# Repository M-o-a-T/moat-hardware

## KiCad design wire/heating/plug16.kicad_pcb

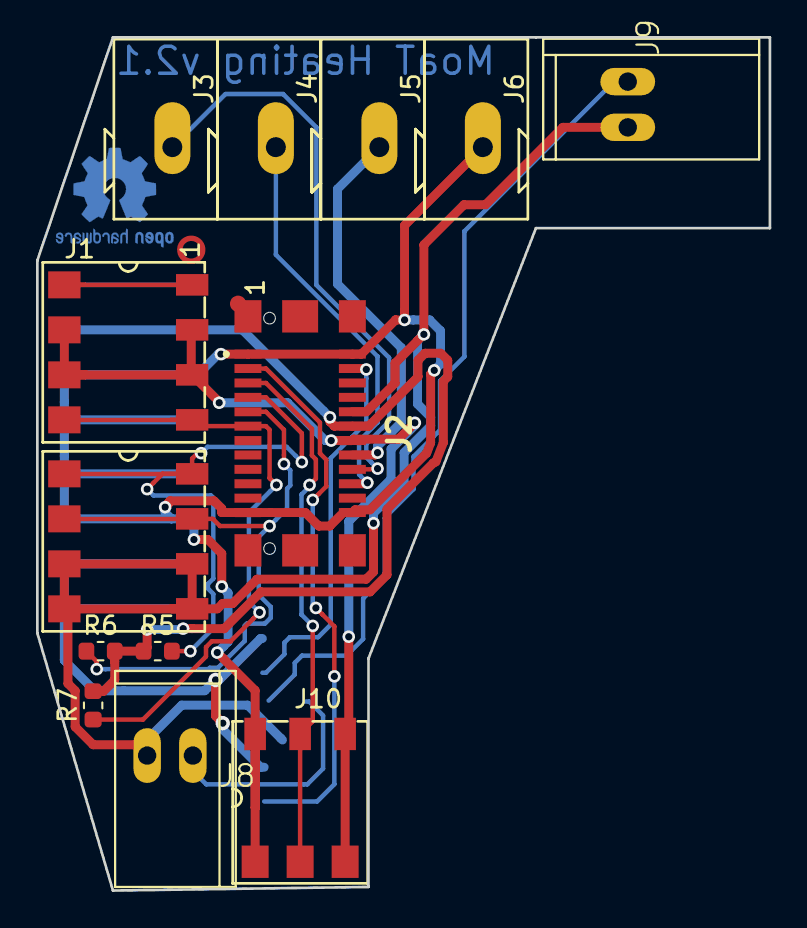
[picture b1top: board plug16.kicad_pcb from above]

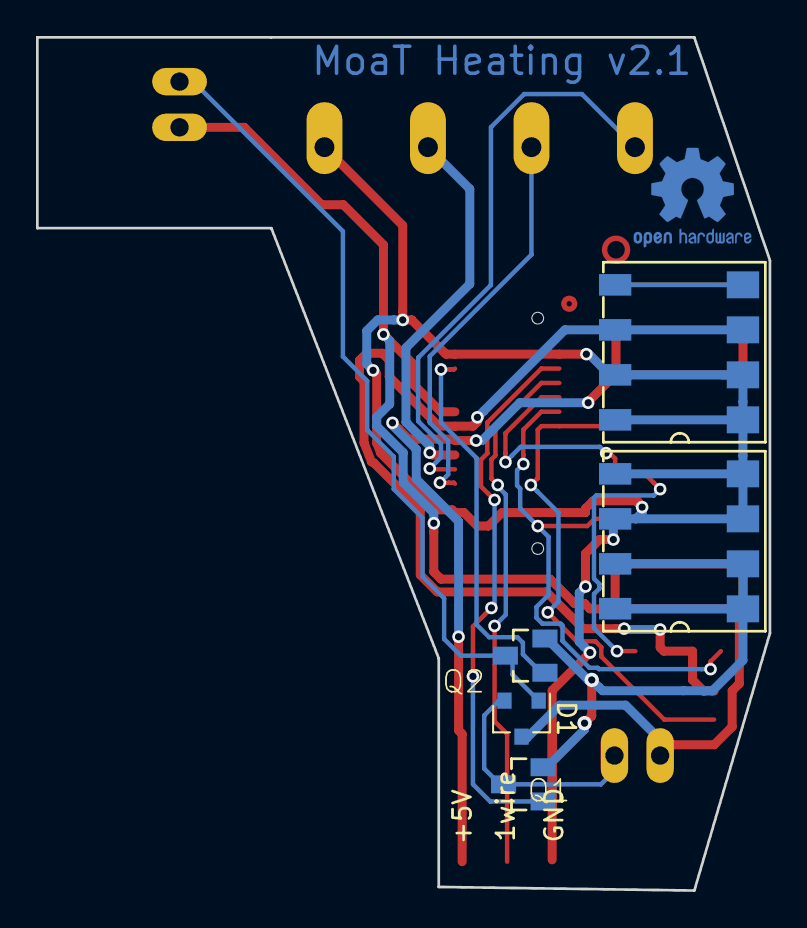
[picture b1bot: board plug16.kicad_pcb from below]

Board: 2 copper layers, 40.7 x 47.4 mm, 15 parts (3 on the bottom side), 16 nets.

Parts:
D1: BAT54C; SOT-23
J1: Moat_Bus_16; Moat_16_2side
J2: Moat_Bus_wire; TE_1775014_socket
J3: SCLK; Wago_Terminal_243
J4: SDA; Wago_Terminal_243
J5: 3V3; Wago_Terminal_243
J6: GND; Wago_Terminal_243
J8: S1; 1X02_GN
J9: S2; 1X02_GN
J10: 1wireConn; AVX_9276_3Pin
Q1, Q2: 2N7002; SOT23
R5, R6, R7: 470; R_0603_1608Metric

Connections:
/S1: J2.3, Q1.1
/S2: J2.4, Q2.1
GNDPWR: J1.14, J1.16, Q1.2, Q2.2
unnamed: D1.1, J9.1, Q2.3
unnamed: D1.2, J8.1, Q1.3
unnamed: D1.3, J1.13, J1.15, J2.10, J8.2, J9.2
unnamed: J1.3, J1.5, J2.14, J10.3
unnamed: J1.4, J2.12, R5.1, R6.2, R7.2
unnamed: J1.7, J2.11, R7.1
unnamed: J1.9, J2.7, R5.2
unnamed: J1.6, J1.8, J1.10, J1.12, J2.1, J2.2, J2.23, J2.24, J6.1, J10.1
unnamed: J1.11, J2.9, R6.1
unnamed: J2.16, J5.1
unnamed: J2.18, J3.1
unnamed: J2.20, J4.1
unnamed: J2.5, J10.2

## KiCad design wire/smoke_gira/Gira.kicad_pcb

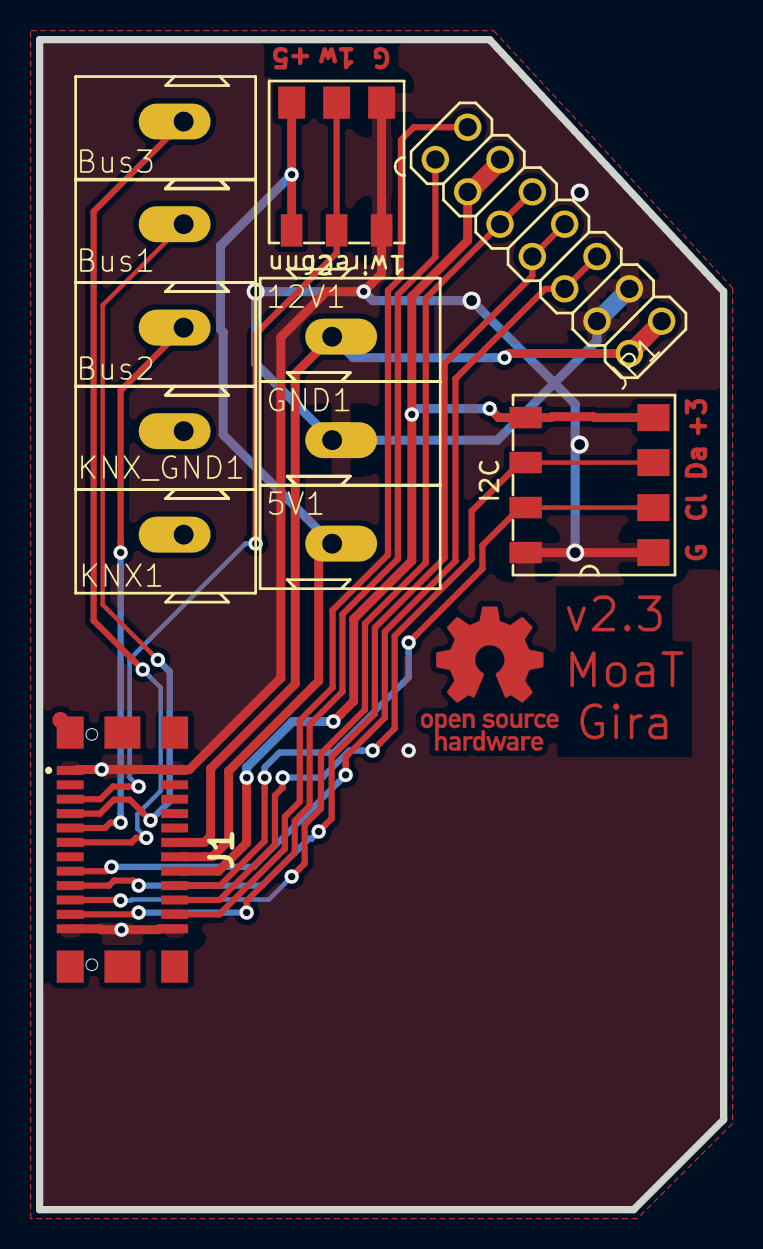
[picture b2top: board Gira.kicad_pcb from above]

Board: 2 copper layers, 38.0 x 65.0 mm, 12 parts (0 on the bottom side), 15 nets.

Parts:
5V1, 12V1: WAGO_243; Wago_Terminal_243
Bus1, Bus2, Bus3: WAGO_243; Wago_Terminal_243
GND1: WAGO_243; Wago_Terminal_243
J1: Moat_Bus_wire; TE_1775014_socket
J2: 1wireConn; AVX_9276_3Pin
J3: I2C; AVX_9276_4Pin
JP1: Gira; 2X07
KNX1: WAGO_243; Wago_Terminal_243
KNX_GND1: WAGO_243; Wago_Terminal_243

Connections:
+3V3: J1.16, J3.4, JP1.11, JP1.12
+5V: 5V1.1, J1.14, J2.3
+12V: 12V1.1, J1.12, JP1.1, JP1.2
/1wire: J1.5, J2.2
/RxD: J1.17, JP1.7, JP1.8
/SCL: J1.18, J3.2
/SDA: J1.20, J3.3
/TEST: J1.21, JP1.14
/TxD: J1.15, JP1.5, JP1.6
/Unk_1: J1.19, JP1.9, JP1.10
/Unk_2: J1.22, JP1.13
GND: GND1.1, J1.1, J1.2, J1.23, J1.24, J2.1, J3.1, JP1.3, JP1.4
unnamed: Bus1.1, J1.7
unnamed: Bus2.1, J1.9
unnamed: Bus3.1, J1.11
